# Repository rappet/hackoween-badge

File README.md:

# Hackoween badge

This has been made with a very hot needle in a very short timeframe.

PCB design is suboptimal.

It is based on the [WCH CH32V003](https://www.wch-ic.com/products/CH32V003.html)
MCU and draws between 11mA and 14mA at 5V.

## Programming

To flash the badge, you need to have a [WCH-LinkE programmer](
https://www.wch-ic.com/products/WCH-Link.html) and the
[`wlink` CLI tool](https://github.com/ch32-rs/wlink).

NOTE: The older WCH-Link (without E) does _not_ work!

Connect as follows:

- `TP3` is the _SWDIO_ pin
- `TP1` is 5V VCC
- `TP2` is GND (ground)

In the `firmware/` directory, run:
```sh
cargo run --release
```

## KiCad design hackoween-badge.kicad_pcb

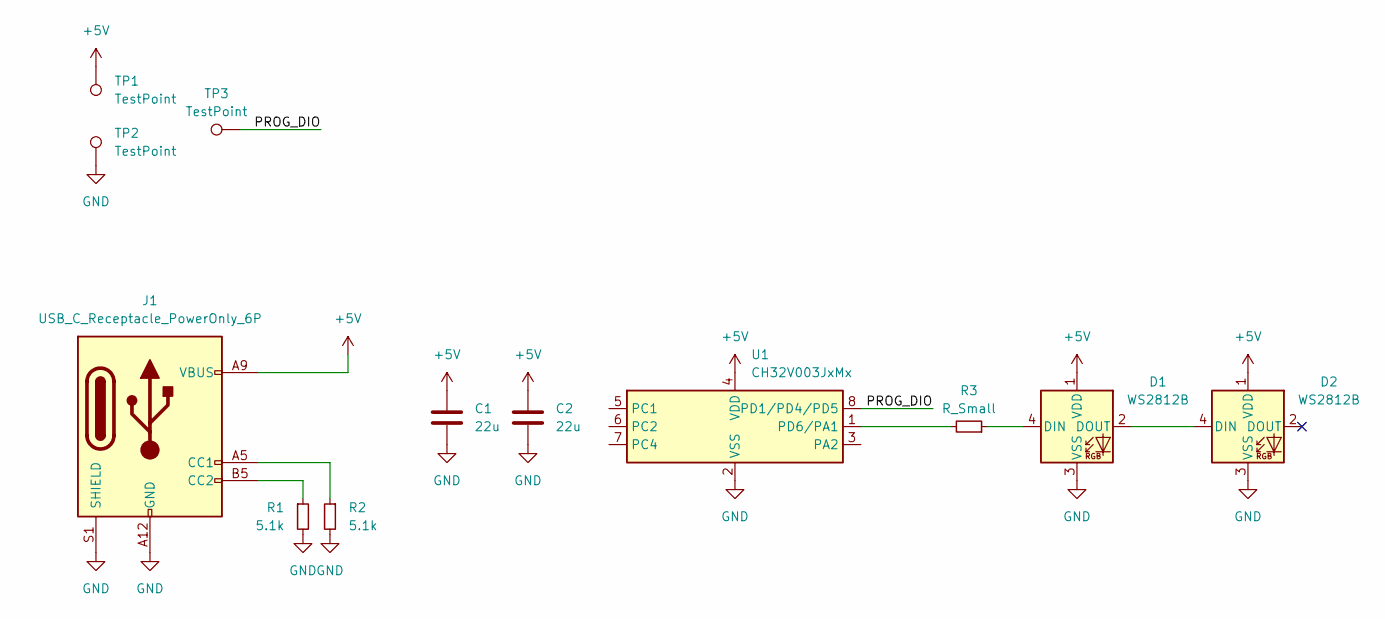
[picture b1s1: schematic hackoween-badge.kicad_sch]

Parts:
C1, C2: 22u; C_1206_3216Metric
D1, D2: WS2812B; LED_WS2812B_PLCC4_5.0x5.0mm_P3.2mm_Flipped
J1: USB_C_Receptacle_PowerOnly_6P; USB_C_Receptacle_HRO_TYPE-C-31-M-17
R1, R2: 5.1k; R_0603_1608Metric_Pad0.98x0.95mm_HandSolder
R3: R_Small; R_0603_1608Metric_Pad0.98x0.95mm_HandSolder
TP1, TP2, TP3: TestPoint; TestPoint_Pad_D4.0mm
U1: CH32V003JxMx; SOP-8_3.9x4.9mm_P1.27mm

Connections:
+5V: C1.1, C2.1, D1.1 (VDD), D2.1 (VDD), J1.A9 (VBUS), J1.B9 (VBUS), TP1.1, U1.4 (VDD)
/PROG_DIO: TP3.1, U1.8 (PD1/PD4/PD5)
GND: C1.2, C2.2, D1.3 (VSS), D2.3 (VSS), J1.A12 (GND), J1.B12 (GND), J1.S1 (SHIELD), R1.2, R2.2, TP2.1, U1.2 (VSS)
unnamed: D1.4 (DIN), R3.1
unnamed: D1.2 (DOUT), D2.4 (DIN)
unnamed: J1.A5 (CC1), R2.1
unnamed: J1.B5 (CC2), R1.1
unnamed: R3.2, U1.1 (PD6/PA1)

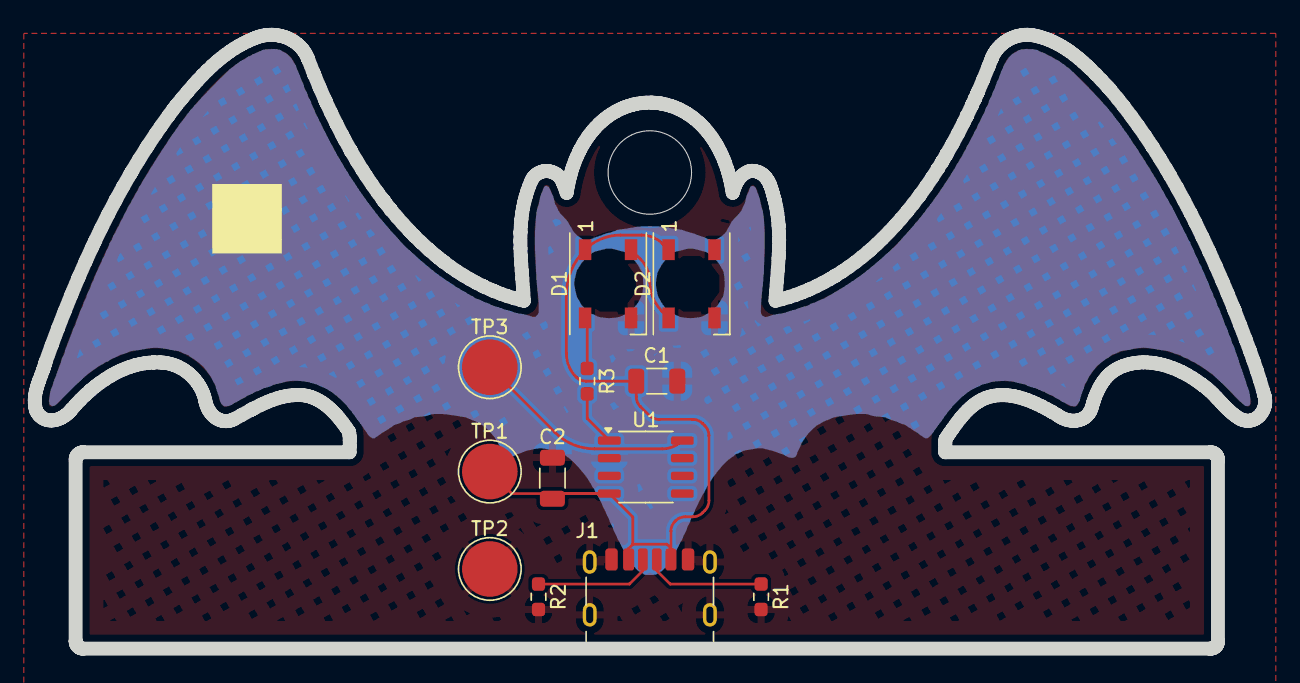
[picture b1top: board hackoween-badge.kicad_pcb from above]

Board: 2 copper layers, 88.5 x 44.1 mm, 12 parts (0 on the bottom side), 8 nets.

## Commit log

2024-11-03 Add PCB design
2024-11-03 WIP: Add Firmware
2024-11-03 Add warning
2024-11-06 firmware: Fix missing memory-x issure
2024-11-06 firmware: Add target to .gitignore
2024-11-06 Cargo.toml: put comments above, switch to ch32v003j4m6, upgrade crates
    Based on a diff against a freshly bootstrapped project using
    https://github.com/ch32-rs/ch32-hal-template
2024-11-06 add rust-toolchain.toml to pin Rust nightly version
2024-11-06 add photo, firmware builds fine now
2024-11-07 README: document MCU in use and power drawn
2024-11-17 README: document how to flash the badge
2025-07-08 schematic: Resized to A5
2025-07-08 schematic: Plotted as PDF
